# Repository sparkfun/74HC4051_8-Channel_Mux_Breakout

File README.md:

SparkFun Multiplexer Breakout - 8 Channel (74HC4051)
========================================

[*SparkFun Multiplexer Breakout - 8 Channel (74HC4051) (SKU)*](https://www.sparkfun.com/products/13906)

The SparkFun Multiplexer Breakout provides access to all pins and features of the 74HC4051, an 8-channel analog multiplexer/demultiplexer. The 74HC4051 allows you to turn four I/O pins into eight multi-functional, individually-selectable signals, which can be used do everything from driving eight LEDs to monitoring eight potentiometers.

Repository Contents
-------------------

* **/Firmware** - Example code 
* **/Hardware** - Eagle design files (.brd, .sch)
* **/Production** - Production panel files (.brd)

Documentation
--------------
* **[Hookup Guide](https://learn.sparkfun.com/tutorials/multiplexer-breakout-hookup-guide)** - Basic hookup guide for the Multiplexer Breakout - 8 Channel (74HC4051).
* **[SparkFun Fritzing repo](https://github.com/sparkfun/Fritzing_Parts)** - Fritzing diagrams for SparkFun products.
* **[SparkFun 3D Model repo](https://github.com/sparkfun/3D_Models)** - 3D models of SparkFun products. 

Product Versions
----------------
* [BOB-13906](https://www.sparkfun.com/products/13906)- Basic part and short description here

Version History
---------------
* [v1.0](https://github.com/sparkfun/74HC4051_8-Channel_Mux_Breakout/tree/V_1.0) - Initial hardware release

License Information
-------------------

This product is _**open source**_! 

Please review the LICENSE.md file for license information. 

If you have any questions or concerns on licensing, please contact techsupport@sparkfun.com.

Distributed as-is; no warranty is given.

- Your friends at SparkFun.

_<COLLABORATION CREDIT>_

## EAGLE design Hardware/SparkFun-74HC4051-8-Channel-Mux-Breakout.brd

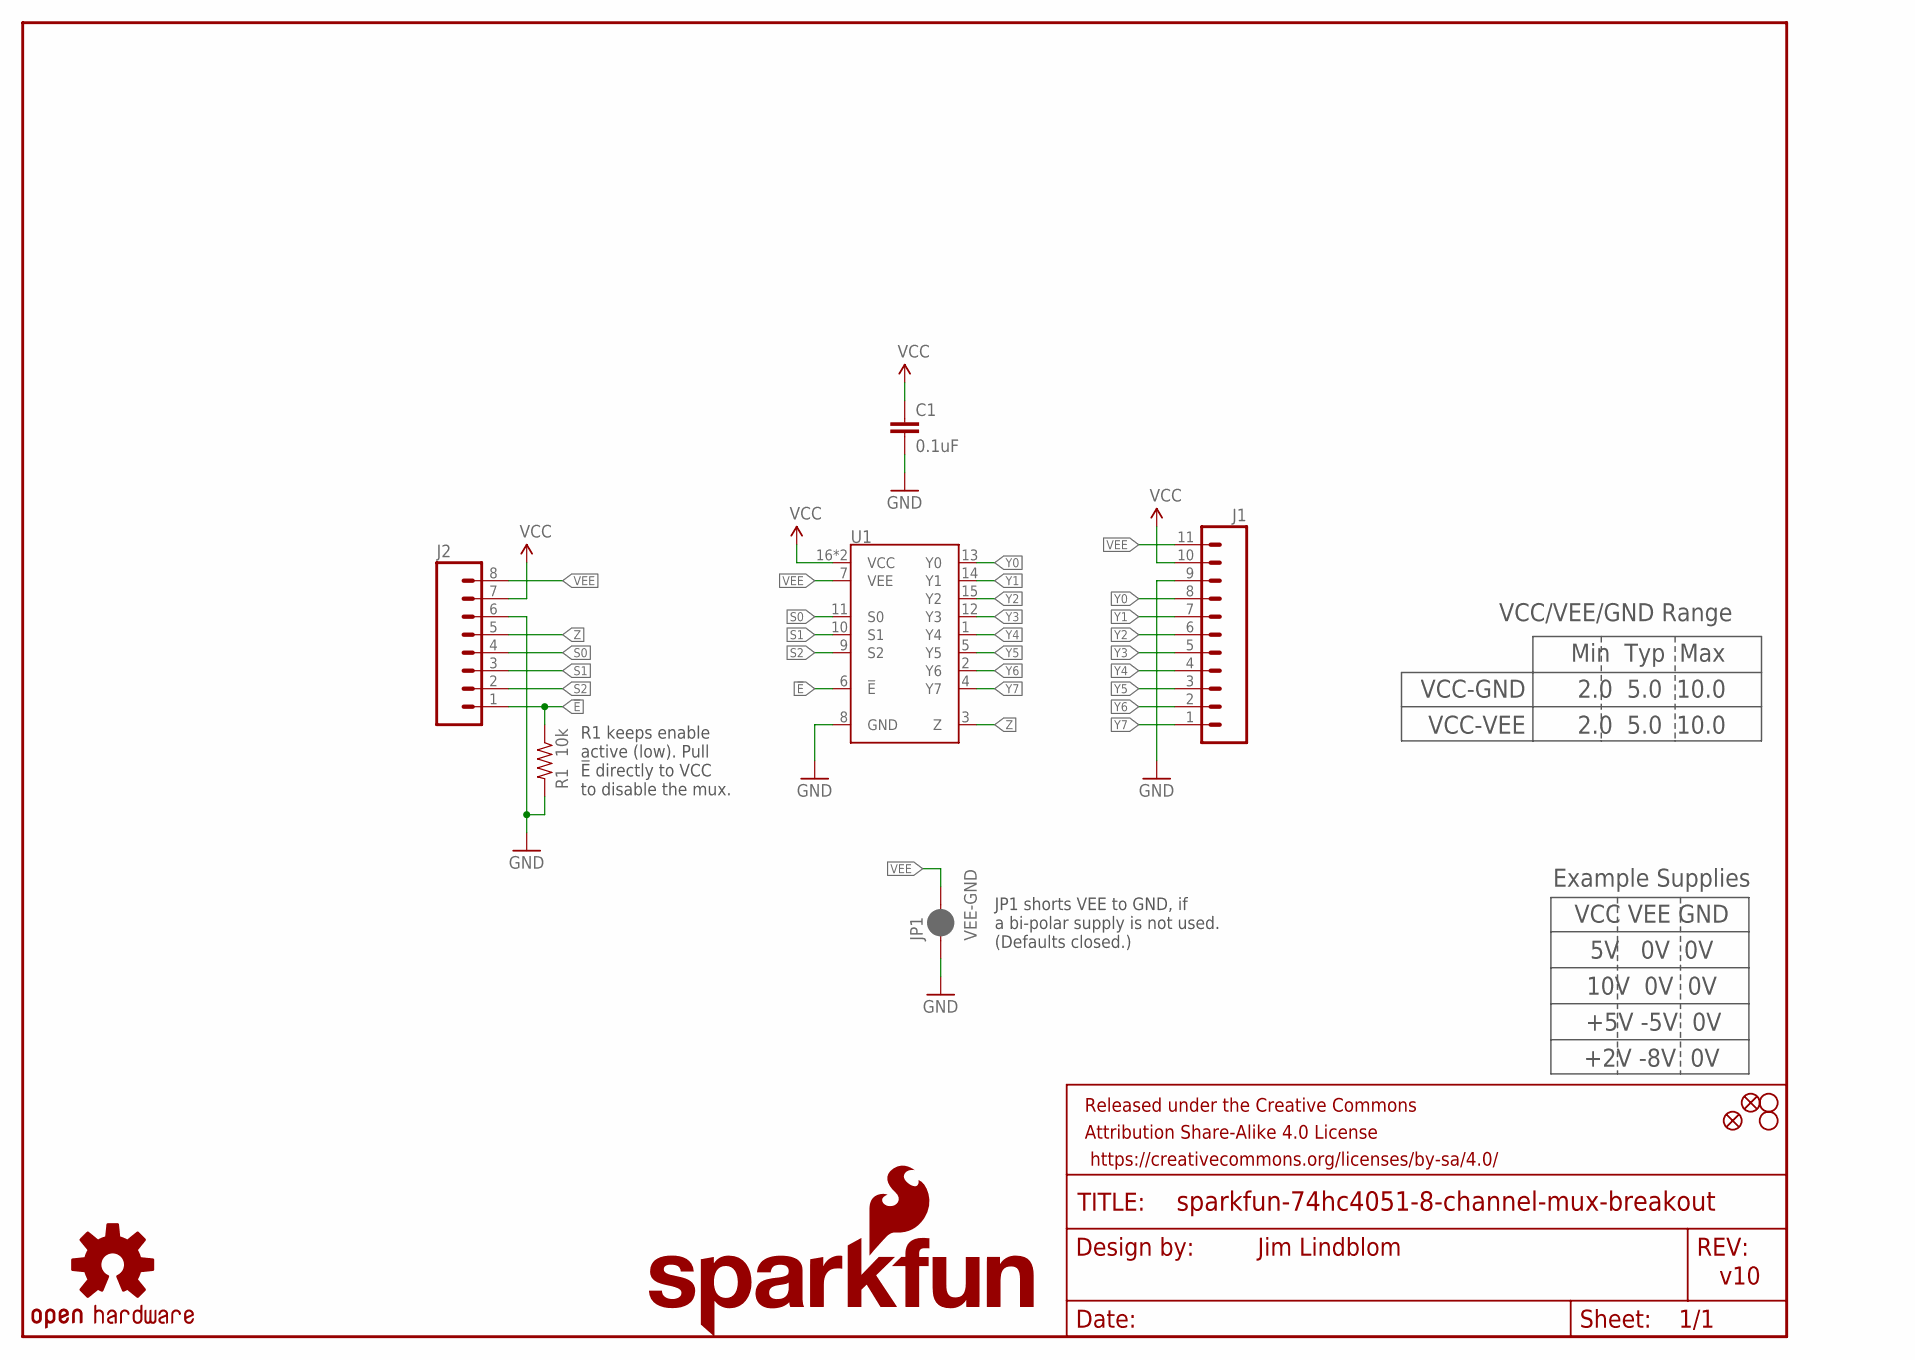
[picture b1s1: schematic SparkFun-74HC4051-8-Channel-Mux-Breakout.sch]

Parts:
C1: 0.1uF; 0603
FD1, FD2: FIDUCIAL1X2; FIDUCIAL-1X2
FRAME1: FRAME-LETTER; CREATIVE_COMMONS
H1, H2: STAND-OFF
J1: M11PTH; 1X11
J2: M08; 1X08_ROUND
JP1: VEE-GND; PAD-JUMPER-2-NC_BY_PASTE_NO_SILK
LOGO1: SFE_LOGO_FLAME.1_INCH; SFE_LOGO_FLAME_.1
LOGO2: OSHW-LOGOMINI; OSHW-LOGO-MINI
LOGO3: SFE_LOGO_NAME.1_INCH; SFE_LOGO_NAME_.1
R1: 10k; 0603
U1: 74HC4051BQ; DHVQFN-16-2.5X3.5MM

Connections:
!E!: J2.1, R1.1, U1.6 (!E!)
GND: C1.2, J1.9, J2.6, JP1.1, R1.2, U1.8 (GND)
S0: J2.4, U1.11 (S0)
S1: J2.3, U1.10 (S1)
S2: J2.2, U1.9 (S2)
VCC: C1.1, J1.10, J2.7, U1.16 (VCC), U1.EP (VCC)
VEE: J1.11, J2.8, JP1.2, U1.7 (VEE)
Y0: J1.8, U1.13 (Y0)
Y1: J1.7, U1.14 (Y1)
Y2: J1.6, U1.15 (Y2)
Y3: J1.5, U1.12 (Y3)
Y4: J1.4, U1.1 (Y4)
Y5: J1.3, U1.5 (Y5)
Y6: J1.2, U1.2 (Y6)
Y7: J1.1, U1.4 (Y7)
Z: J2.5, U1.3 (Z)

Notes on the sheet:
VCC-GND
VCC-VEE
Min Typ Max
2.0 5.0 10.0
v10
Jim Lindblom
JP1 shorts VEE to GND, if a bi-polar supply is not used. (Defaults closed.)
R1 keeps enable active (low). Pull !E! directly to VCC to disable the mux.
VCC VEE GND
10V 0V 0V
+5V -5V 0V
+2V -8V 0V
5V 0V 0V
Example Supplies
VCC/VEE/GND Range

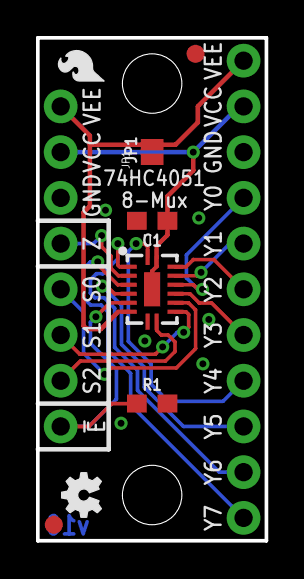
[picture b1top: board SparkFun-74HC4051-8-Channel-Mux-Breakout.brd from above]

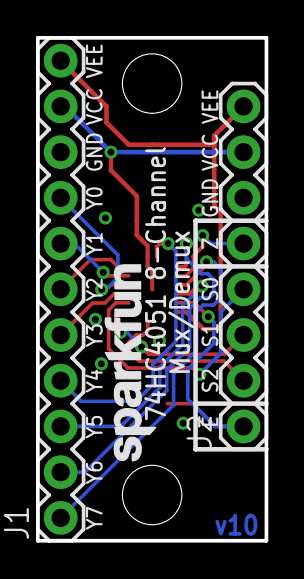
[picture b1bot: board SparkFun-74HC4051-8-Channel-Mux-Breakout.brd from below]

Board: 2 copper layers, 12.7 x 27.9 mm, 14 parts (3 on the bottom side), 16 nets.

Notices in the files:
parts and their libraries:
SparkFun-Capacitors: Licensing: Creative Commons ShareAlike 4.0 International - https://creativecommons.org/licenses/by-sa/4.0
SparkFun-Aesthetics: Released under the Creative Commons Attribution Share-Alike 4.0 License
SparkFun-Aesthetics: https://creativecommons.org/licenses/by-sa/4.0
